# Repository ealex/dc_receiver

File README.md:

# dc_receiver
simple DC receiver based on AA7EE's "The VE7BPO Direct Conversion Receiver Mainframe"

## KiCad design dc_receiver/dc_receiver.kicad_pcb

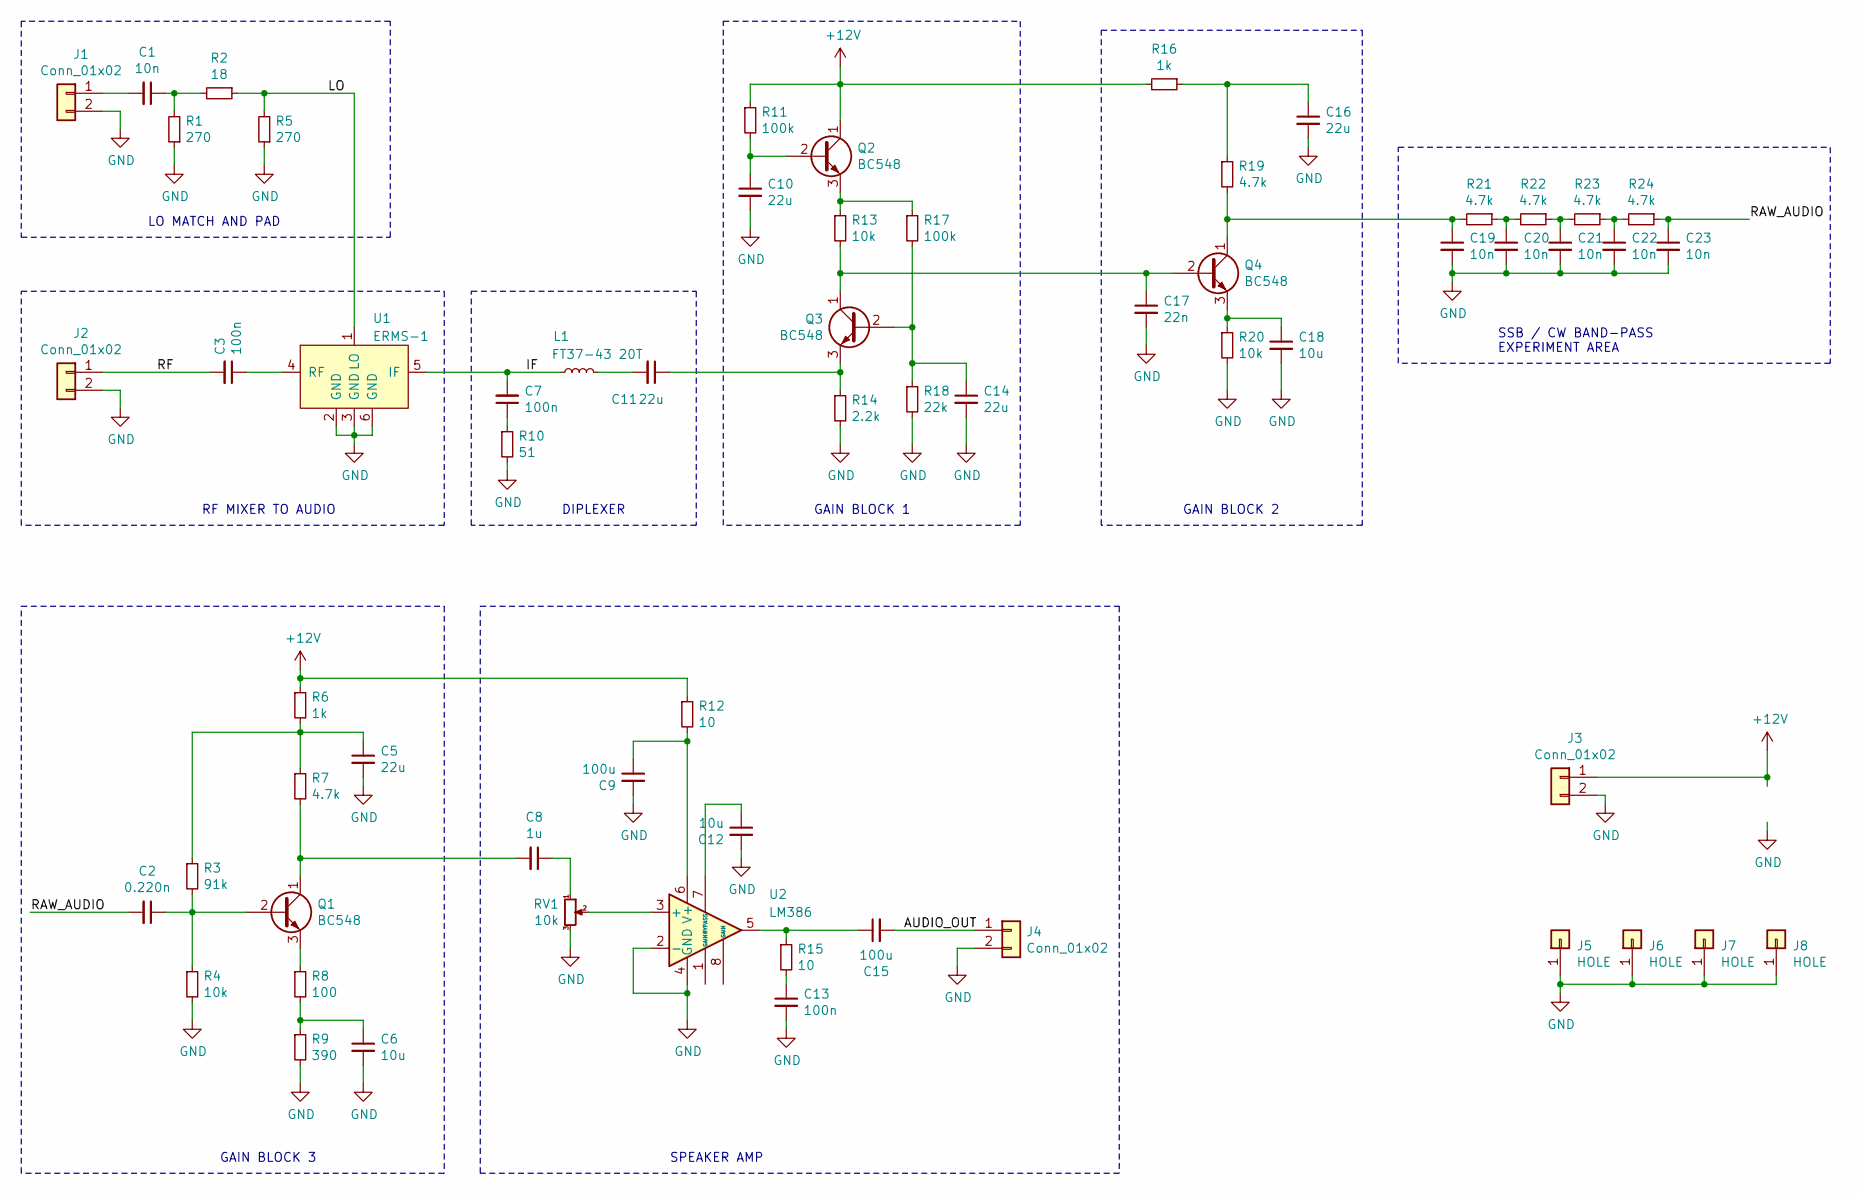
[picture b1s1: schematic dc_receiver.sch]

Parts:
C1, C19, C20, C21, C22, C23: 10n; C_1206_3216Metric_Pad1.42x1.75mm_HandSolder
C2: 0.220n; C_1206_3216Metric_Pad1.42x1.75mm_HandSolder
C3, C7, C13: 100n; C_1206_3216Metric_Pad1.42x1.75mm_HandSolder
C5, C10, C11, C14, C16: 22u; CP_Radial_D6.3mm_P2.50mm
C6, C12, C18: 10u; CP_Radial_D5.0mm_P2.00mm
C8: 1u; C_1206_3216Metric_Pad1.42x1.75mm_HandSolder
C9, C15: 100u; CP_Radial_D8.0mm_P3.50mm
C17: 22n; C_1206_3216Metric_Pad1.42x1.75mm_HandSolder
J1, J2, J3, J4: Conn_01x02; PinHeader_1x02_P2.54mm_Vertical
J5, J6, J7, J8: HOLE
L1: FT37-43 20T; ft37-43-choke
Q1, Q2, Q3, Q4: BC548; TO-92_Inline_Wide
R1, R5: 270; R_1206_3216Metric_Pad1.42x1.75mm_HandSolder
R2: 18; R_1206_3216Metric_Pad1.42x1.75mm_HandSolder
R3: 91k; R_1206_3216Metric_Pad1.42x1.75mm_HandSolder
R4, R13, R20: 10k; R_1206_3216Metric_Pad1.42x1.75mm_HandSolder
R6, R16: 1k; R_1206_3216Metric_Pad1.42x1.75mm_HandSolder
R7, R19, R21, R22, R23, R24: 4.7k; R_1206_3216Metric_Pad1.42x1.75mm_HandSolder
R8: 100; R_1206_3216Metric_Pad1.42x1.75mm_HandSolder
R9: 390; R_1206_3216Metric_Pad1.42x1.75mm_HandSolder
R10: 51; R_1206_3216Metric_Pad1.42x1.75mm_HandSolder
R11, R17: 100k; R_1206_3216Metric_Pad1.42x1.75mm_HandSolder
R12, R15: 10; R_1206_3216Metric_Pad1.42x1.75mm_HandSolder
R14: 2.2k; R_1206_3216Metric_Pad1.42x1.75mm_HandSolder
R18: 22k; R_1206_3216Metric_Pad1.42x1.75mm_HandSolder
RV1: 10k; PinHeader_1x03_P2.54mm_Vertical
U1: ERMS-1
U2: LM386; SO-8_3.9x4.9mm_P1.27mm

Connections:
+12V: J3.1, Q2.1 (C), R6.1, R11.1, R12.1, R16.2
/AUDIO_OUT: C15.2, J4.1
/IF: C7.2, L1.1, U1.5 (IF)
/LO: R2.1, R5.2, U1.1 (LO)
/RAW_AUDIO: C2.2, C23.1, R24.1
/RF: C3.2, J2.1
GND: C5.2, C6.2, C9.2, C10.2, C12.2, C13.2, C14.2, C16.2, C17.2, C18.2, C19.2, C20.2, C21.2, C22.2, C23.2, J1.2, J2.2, J3.2, J4.2, J5.1, J6.1, J7.1, J8.1, R1.1, R4.2, R5.1, R9.2, R10.2, R14.2, R18.2, R20.2, RV1.3, U1.2 (GND), U1.3 (GND), U1.6 (GND), U2.2 (-), U2.4 (GND)
unnamed: C1.1, R1.2, R2.2
unnamed: C1.2, J1.1
unnamed: C2.1, Q1.2 (B), R3.2, R4.1
unnamed: C3.1, U1.4 (RF)
unnamed: C5.1, R3.1, R6.2, R7.1
unnamed: C6.1, R8.2, R9.1
unnamed: C7.1, R10.1
unnamed: C8.1, RV1.1
unnamed: C8.2, Q1.1 (C), R7.2
unnamed: C9.1, R12.2, U2.6 (V+)
unnamed: C10.1, Q2.2 (B), R11.2
unnamed: C11.1, Q3.3 (E), R14.1
unnamed: C11.2, L1.2
unnamed: C12.1, U2.7 (BYPASS)
unnamed: C13.1, R15.2
unnamed: C14.1, Q3.2 (B), R17.2, R18.1
unnamed: C15.1, R15.1, U2.5
unnamed: C16.1, R16.1, R19.1
unnamed: C17.1, Q3.1 (C), Q4.2 (B), R13.2
unnamed: C18.1, Q4.3 (E), R20.1
unnamed: C19.1, Q4.1 (C), R19.2, R21.2
unnamed: C20.1, R21.1, R22.2
unnamed: C21.1, R22.1, R23.2
unnamed: C22.1, R23.1, R24.2
unnamed: Q1.3 (E), R8.1
unnamed: Q2.3 (E), R13.1, R17.1
unnamed: RV1.2, U2.3 (+)

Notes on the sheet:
GAIN BLOCK 1
GAIN BLOCK 2
SSB / CW BAND-PASS EXPERIMENT AREA
RF MIXER TO AUDIO
LO MATCH AND PAD
DIPLEXER
GAIN BLOCK 3
SPEAKER AMP

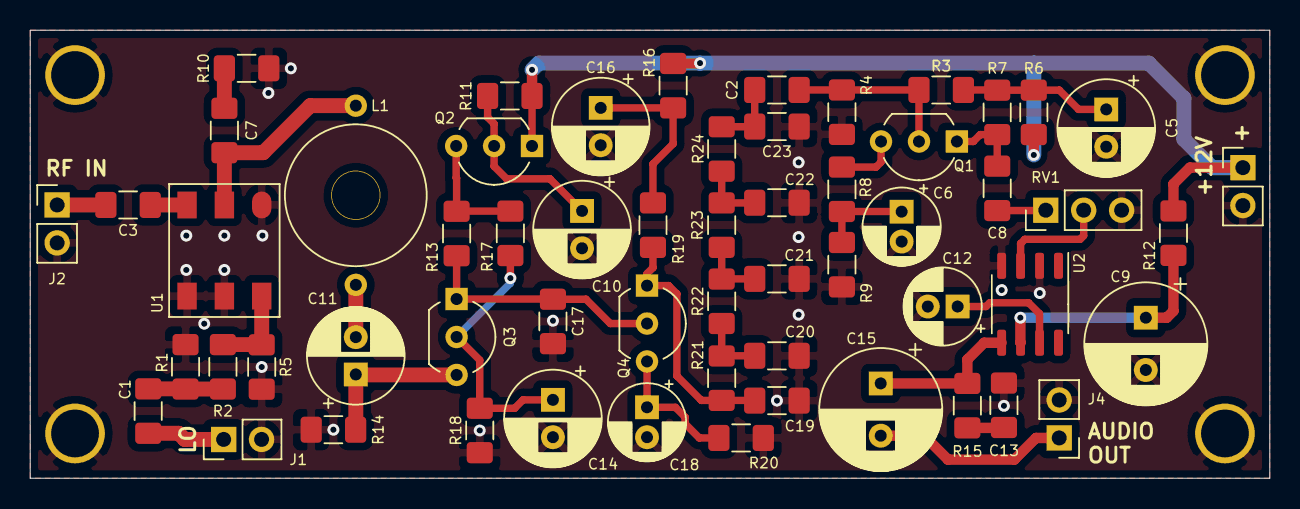
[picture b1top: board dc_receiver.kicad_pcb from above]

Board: 2 copper layers, 83.0 x 30.0 mm, 62 parts (0 on the bottom side), 34 nets.

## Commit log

2022-03-02 add project documentation
2022-03-02 schematic
2022-03-09 finish schenmatic add layout
2022-03-09 add renders, pdf schematic, ready for export
2022-03-11 order pcb
2022-03-11 start control fw
